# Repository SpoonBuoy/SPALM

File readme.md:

# Usage 
1)  Clone via `git clone https://github.com/SpoonBuoy/SPALM.git`
2) `cd SPALM`
3)  Copy all libs and paste them in Eagle libraries folder (which would be something like this C:Eagle\libraries)

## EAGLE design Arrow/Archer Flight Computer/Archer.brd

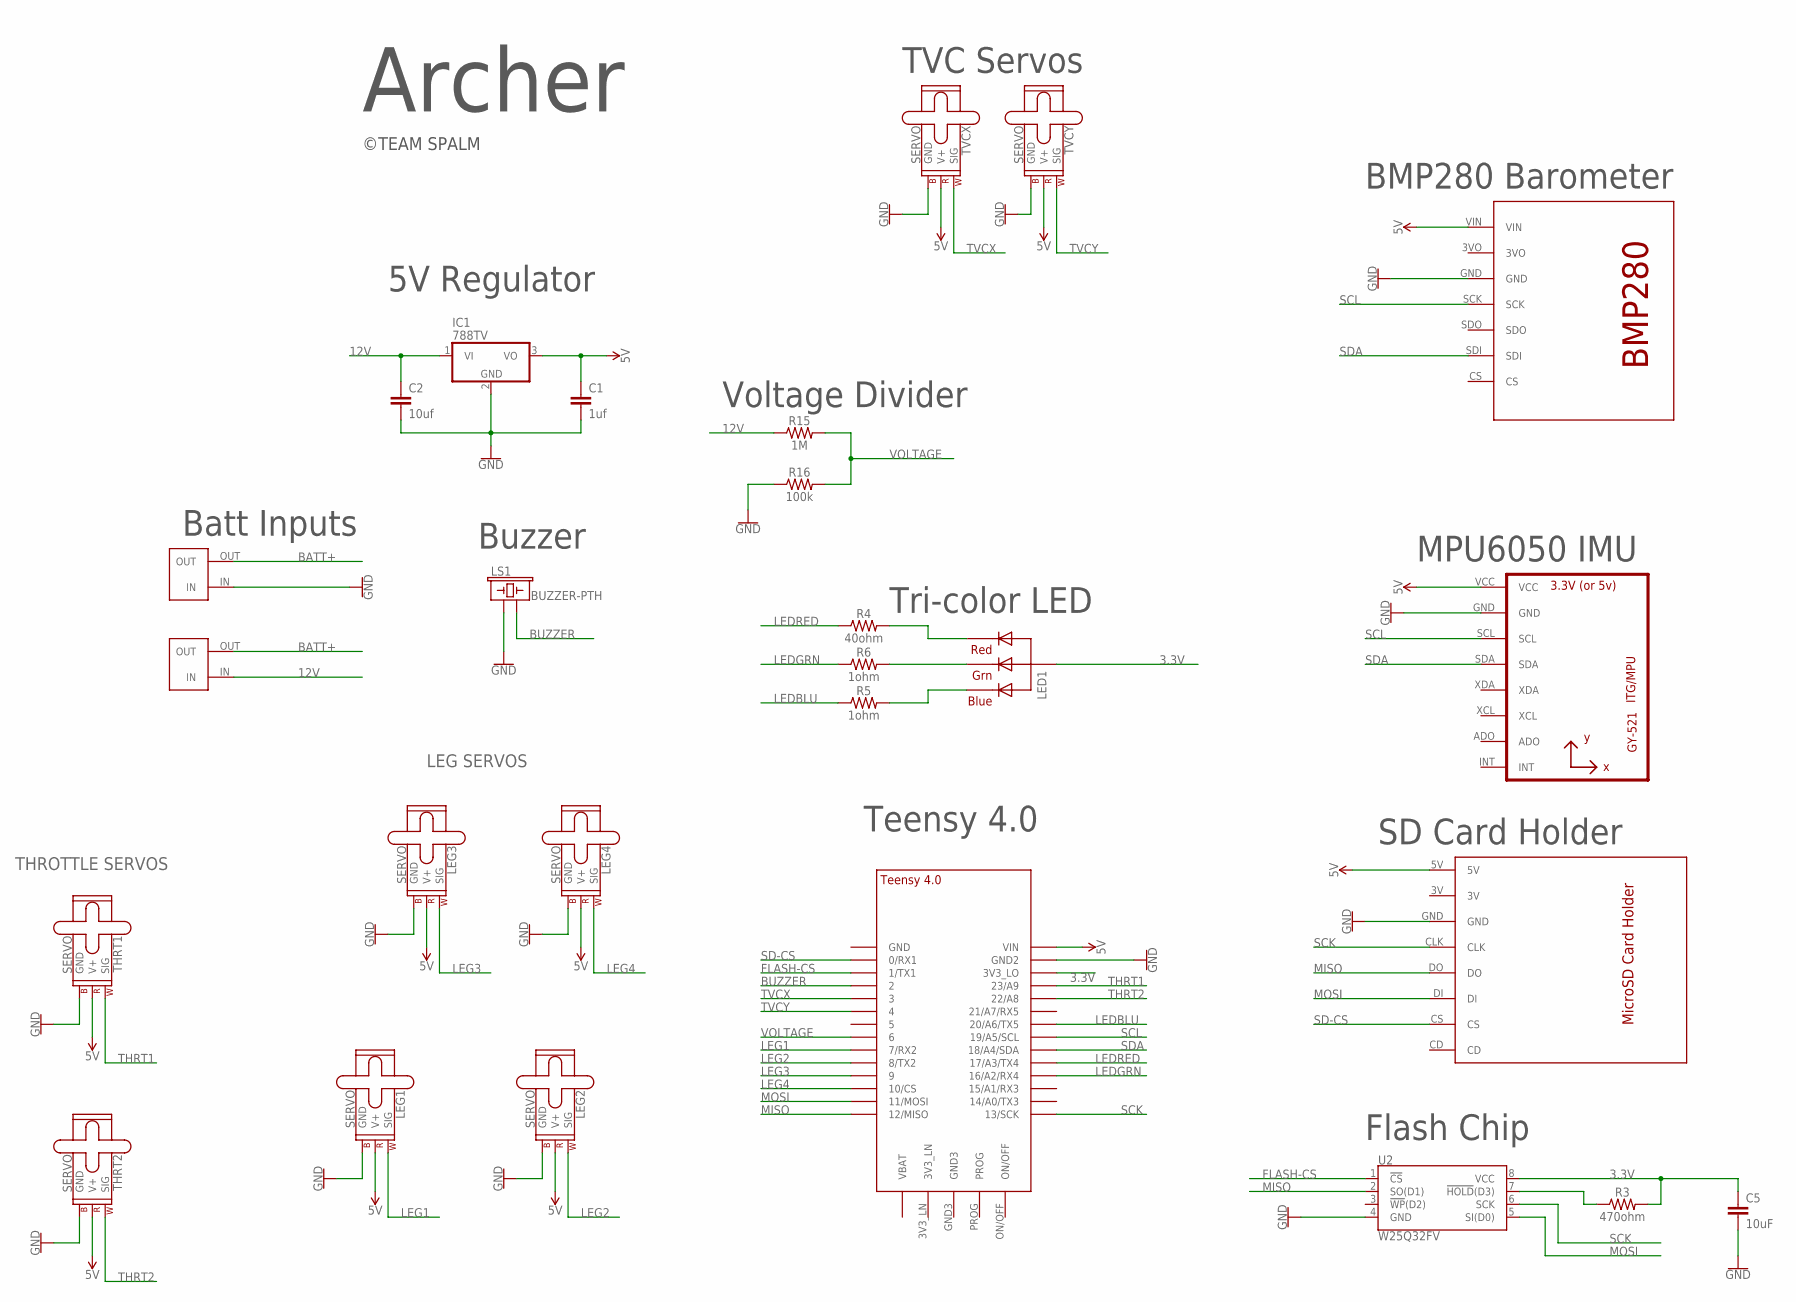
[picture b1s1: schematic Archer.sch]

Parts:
C1: 1uf; CAP-PTH-2.54
C2: 10uf; CAP-PTH-2.54
C5: 10uF; CAP-PTH-2.54
IC1: 788TV; TO220V
LED1: RGBLED_CA-5MM; LED5MMRGB
LEG1, LEG2, LEG3, LEG4: SERVO; 1X03
LS1: BUZZER-PTH; BUZZER-12MM
R3: 470ohm; AXIAL-0.3
R4: 40ohm; AXIAL-0.3
R5, R6: 1ohm; AXIAL-0.3
R15: 1M; AXIAL-0.3
R16: 100k; AXIAL-0.3
TEENSY_4.0: TEENSY_4.0
THRT1, THRT2: SERVO; 1X03
TVCX: SERVO; 1X03
TVCY: SERVO; 1X03
U1: GY-521MPU6050; GY-521
U2: W25Q32FV; SOIC-8
U$2: BMP280
U$3: MICROSDCARDHOLDER; SDCARDHOLDER
U$8, U$9: BLACKTERMBLOCK

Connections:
3.3V: C5.1, LED1.2 (VCC), R3.P$2 (2), TEENSY_4.0.3V3_LO, U2.8 (VCC)
5V: C1.1, IC1.3 (VO), LEG1.2 (V+), LEG2.2 (V+), LEG3.2 (V+), LEG4.2 (V+), TEENSY_4.0.VIN, THRT1.2 (V+), THRT2.2 (V+), TVCX.2 (V+), TVCY.2 (V+), U1.VCC, U$2.VIN, U$3.5V
12V: C2.1, IC1.1 (VI), R15.P$1 (1), U$9.IN
BATT+: U$8.OUT, U$9.OUT
BUZZER: LS1.- (2), TEENSY_4.0.2
FLASH-CS: TEENSY_4.0.1/TX (1/TX1), U2.1 (!CS!)
GND: C1.2, C2.2, C5.2, IC1.2 (GND), LEG1.3 (GND), LEG2.3 (GND), LEG3.3 (GND), LEG4.3 (GND), LS1.+ (1), R16.P$1 (1), TEENSY_4.0.GND2, THRT1.3 (GND), THRT2.3 (GND), TVCX.3 (GND), TVCY.3 (GND), U1.GND, U2.4 (GND), U$2.GND, U$3.GND, U$8.IN
LEDBLU: R5.P$1 (1), TEENSY_4.0.20/A6 (20/A6/TX5)
LEDGRN: R6.P$1 (1), TEENSY_4.0.16/A2 (16/A2/RX4)
LEDRED: R4.P$1 (1), TEENSY_4.0.17/A3 (17/A3/TX4)
LEG1: LEG1.1 (SIG), TEENSY_4.0.7 (7/RX2)
LEG2: LEG2.1 (SIG), TEENSY_4.0.8 (8/TX2)
LEG3: LEG3.1 (SIG), TEENSY_4.0.9/CS (9)
LEG4: LEG4.1 (SIG), TEENSY_4.0.10/CS
MISO: TEENSY_4.0.12/MISO, U2.2 (SO(D1)), U$3.DO
MOSI: TEENSY_4.0.11/MOSI, U2.5 (SI(D0)), U$3.DI
unnamed: LED1.1 (RED), R4.P$2 (2)
unnamed: R3.P$1 (1), U2.7 (!HOLD!(D3))
unnamed: LED1.3 (GREEN), R6.P$2 (2)
unnamed: LED1.4 (BLUE), R5.P$2 (2)
SCK: TEENSY_4.0.13/SCK, U2.6 (SCK), U$3.CLK
SCL: TEENSY_4.0.19/A5/SCL, U1.SCL, U$2.SCK
SD-CS: TEENSY_4.0.0/RX (0/RX1), U$3.CS
SDA: TEENSY_4.0.18/A4/SDA, U1.SDA, U$2.SDI
THRT1: TEENSY_4.0.23/A9, THRT1.1 (SIG)
THRT2: TEENSY_4.0.22/A8, THRT2.1 (SIG)
TVCX: TEENSY_4.0.3/CANTX (3), TVCX.1 (SIG)
TVCY: TEENSY_4.0.4/CANRX (4), TVCY.1 (SIG)
VOLTAGE: R15.P$2 (2), R16.P$2 (2), TEENSY_4.0.6

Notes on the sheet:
5V Regulator
TVC Servos
Batt Inputs
Buzzer
Tri-color LED
Voltage Divider
Flash Chip
SD Card Holder
MPU6050 IMU
BMP280 Barometer
Archer
©TEAM SPALM
Teensy 4.0
LEG SERVOS
THROTTLE SERVOS

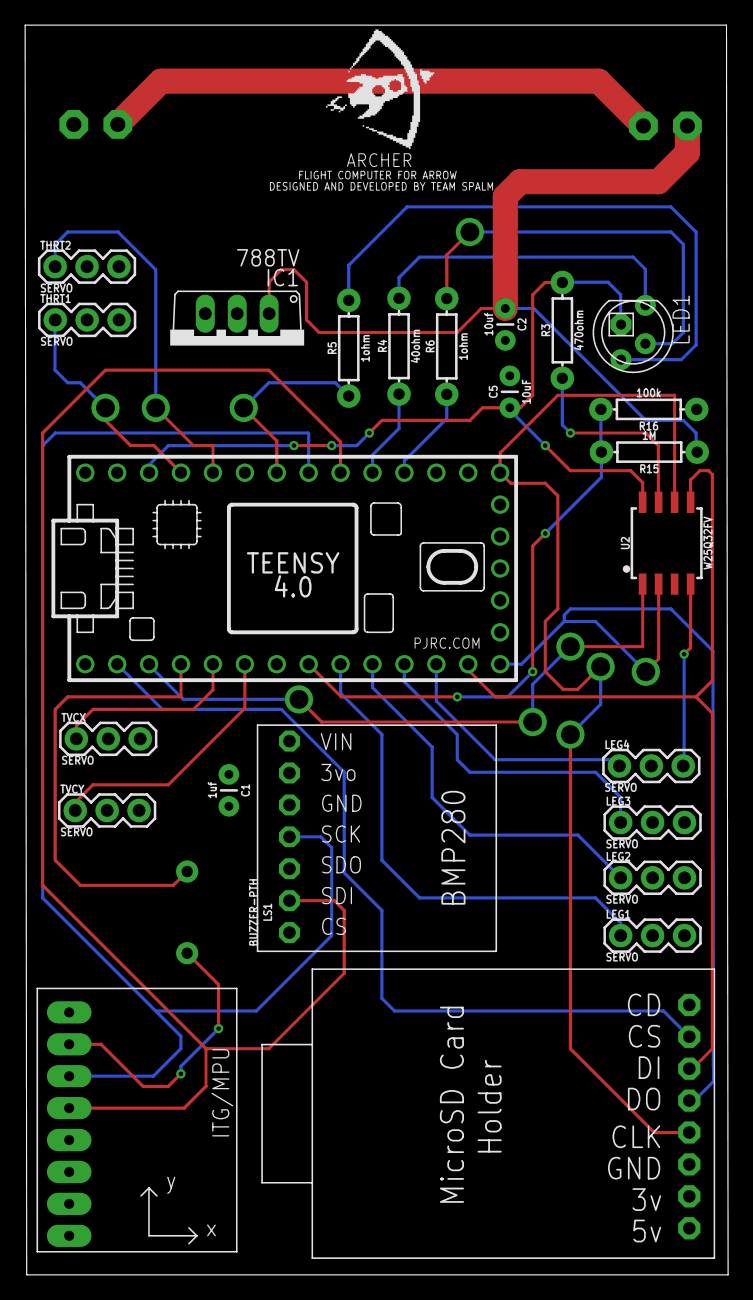
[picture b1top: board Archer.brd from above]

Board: 2 copper layers, 55.9 x 99.5 mm, 27 parts (0 on the bottom side), 29 nets.

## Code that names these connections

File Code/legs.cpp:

#include <Wire.h>
#include <Adafruit_Sensor.h>
#include <Adafruit_BMP280.h>
#include <Servo.h>

Adafruit_BMP280 bmp;
Servo leg1, leg2, leg3, leg4;

const int bmpAltitudeThreshold = 10;  // Altitude threshold for deploying landing gear in meters

void setup() {
  Wire.begin();
  Serial.begin(9600);

  if (!bmp.begin(0x76)) {
    Serial.println("Could not find a valid BMP280 sensor, check wiring!");
    while (1);
  }

  leg1.attach(2);  // Connect leg1 servo to Teensy digital pin 2
  leg2.attach(3);  // Connect leg2 servo to Teensy digital pin 3
  leg3.attach(4);  // Connect leg3 servo to Teensy digital pin 4
  leg4.attach(5);  // Connect leg4 servo to Teensy digital pin 5

  leg1.write(0);   // Initialize leg1 servo position to 0 degrees
  leg2.write(0);   // Initialize leg2 servo position to 0 degrees
  leg3.write(0);   // Initialize leg3 servo position to 0 degrees
  leg4.write(0);   // Initialize leg4 servo position to 0 degrees
}

void loop() {
  float altitude = bmp.readAltitude();  // Read current altitude from BMP280 sensor

  Serial.print("Altitude: ");
  Serial.print(altitude);
  Serial.println(" meters");

  if (altitude >= bmpAltitudeThreshold) {
    deployLandingGear();  // Deploy landing gear if altitude exceeds threshold
  }

  delay(1000);
}

void deployLandingGear() {
  leg1.write(90);  // Set leg1 servo position to 90 degrees
  leg2.write(90);  // Set leg2 servo position to 90 degrees
  leg3.write(90);  // Set leg3 servo position to 90 degrees
  leg4.write(90);  // Set leg4 servo position to 90 degrees

  delay(2000);  // Wait for 2 seconds to allow landing gear deployment

  leg1.detach();  // Detach leg1 servo to hold its position
  leg2.detach();  // Detach leg2 servo to hold its position
  leg3.detach();  // Detach leg3 servo to hold its position
  leg4.detach();  // Detach leg4 servo to hold its position

  while (1);  // Stop further execution
}

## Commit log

2022-11-11 add eagle libs
2022-11-11 add libs
2022-11-11 add readme
2023-04-04 add work done till now
2023-06-18 add code
2023-06-18 add code complete
2023-06-19 add test code

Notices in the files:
parts and their libraries:
SparkFun-Capacitors: Licensing: Creative Commons ShareAlike 4.0 International - https://creativecommons.org/licenses/by-sa/4.0
